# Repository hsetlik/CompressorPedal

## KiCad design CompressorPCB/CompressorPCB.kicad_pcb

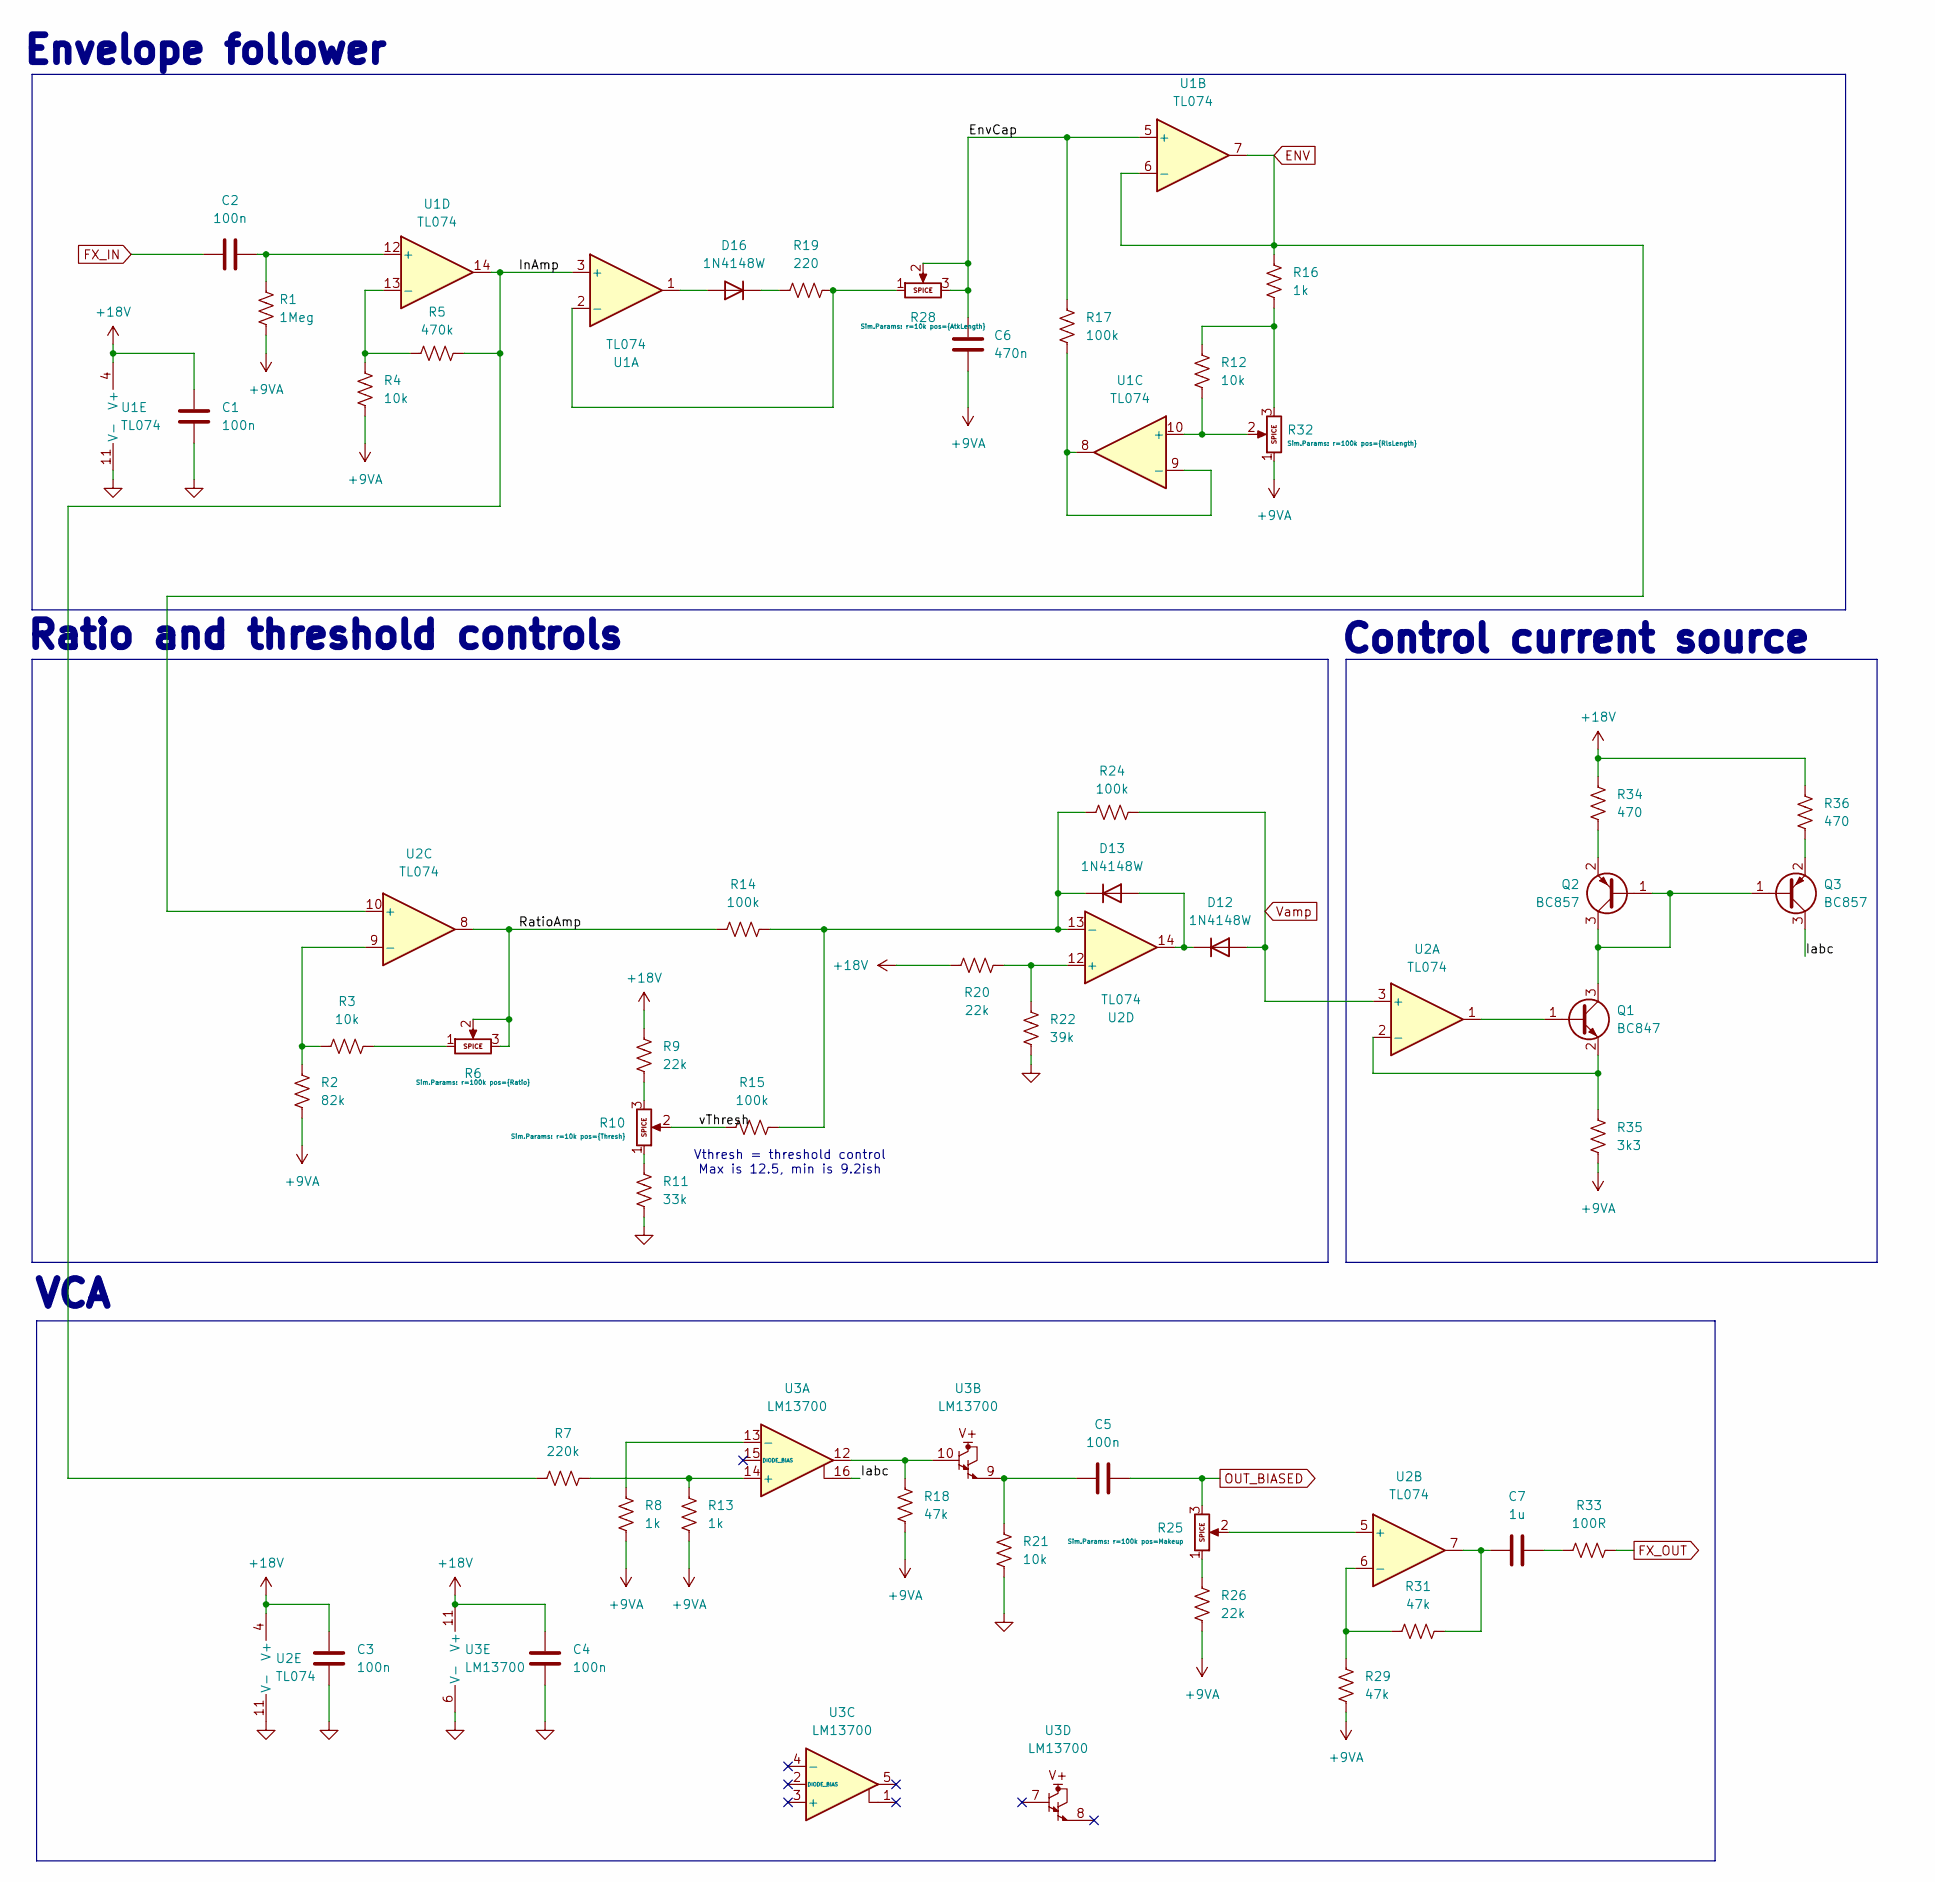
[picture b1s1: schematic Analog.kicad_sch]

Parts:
C1, C2, C3, C4, C5: 100n; C_0805_2012Metric
C6: 470n; C_0805_2012Metric
C7: 1u; C_0805_2012Metric
D12, D13, D16: 1N4148W; D_SOD-123
Q1: BC847; SOT-23
Q2, Q3: BC857; SOT-23
R1: 1Meg; R_0805_2012Metric
R2: 82k; R_0805_2012Metric
R3, R4, R12, R21: 10k; R_0805_2012Metric
R5: 470k; R_0805_2012Metric
R6, R10, R25, R28, R32: Potentiometer; Potentiometer_Alpha_RV16AF_42_Single_Long
R7: 220k; R_0805_2012Metric
R8, R13, R16: 1k; R_0805_2012Metric
R9, R20, R26: 22k; R_0805_2012Metric
R11: 33k; R_0805_2012Metric
R14, R15, R17, R24: 100k; R_0805_2012Metric
R18, R29, R31: 47k; R_0805_2012Metric
R19: 220; R_0805_2012Metric
R22: 39k; R_0805_2012Metric
R33: 100R; R_0805_2012Metric
R34, R36: 470; R_0805_2012Metric
R35: 3k3; R_0805_2012Metric
U1, U2: TL074; SOIC-14_3.9x8.7mm_P1.27mm
U3: LM13700; SOIC-16_3.9x9.9mm_P1.27mm

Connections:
+9VA: C6.2, R1.2, R2.2, R4.2, R8.2, R13.2, R18.2, R26.2, R29.1, R32.1, R35.1; also elsewhere on the board
+18V: C1.2, C3.2, C4.2, R9.1, R20.1, R34.2, R36.2, U1.4 (V+), U2.4 (V+), U3.11 (V+); also elsewhere on the board
/Analog/EnvCap: C6.1, R17.1, R28.2, R28.3, U1.5 (+)
/Analog/Iabc: Q3.3 (C), U3.16
/Analog/InAmp: R5.2, R7.1, U1.3 (+), U1.14
/Analog/RatioAmp: R6.2, R6.3, R14.1, U2.8
/Analog/vThresh: R10.2, R15.1
ENV: R16.1, U1.6 (-), U1.7, U2.10 (+); also elsewhere on the board
FX_IN: C2.1; also elsewhere on the board
FX_OUT: R33.2; also elsewhere on the board
GND: C1.1, C3.1, C4.1, R11.2, R21.2, R22.1, U1.11 (V-), U2.11 (V-), U3.6 (V-); also elsewhere on the board
unnamed: C5.1, R21.1, U3.9
unnamed: C7.1, R31.2, U2.7
unnamed: C7.2, R33.1
unnamed: D12.1 (K), D13.2 (A), U2.14
unnamed: D13.1 (K), R14.2, R15.2, R24.1, U2.13 (-)
unnamed: D16.2 (A), U1.1
unnamed: D16.1 (K), R19.1
unnamed: Q1.1 (B), U2.1
unnamed: Q1.3 (C), Q2.1 (B), Q2.3 (C), Q3.1 (B)
unnamed: Q1.2 (E), R35.2, U2.2 (-)
unnamed: Q2.2 (E), R34.1
unnamed: Q3.2 (E), R36.1
unnamed: R3.2, R6.1
unnamed: R10.1, R11.1
unnamed: R9.2, R10.3
unnamed: R12.1, R16.2, R32.3
unnamed: R18.1, U3.10, U3.12
unnamed: R25.1, R26.1
unnamed: R19.2, R28.1, U1.2 (-)
unnamed: R12.2, R32.2, U1.10 (+)
unnamed: R17.2, U1.8, U1.9 (-)
unnamed: C2.2, R1.1, U1.12 (+)
unnamed: R4.1, R5.1, U1.13 (-)
unnamed: R25.2, U2.5 (+)
unnamed: R29.2, R31.1, U2.6 (-)
unnamed: R2.1, R3.1, U2.9 (-)
unnamed: R20.2, R22.2, U2.12 (+)
unnamed: R7.2, R13.1, U3.14 (+)
unnamed: R8.1, U3.13 (-)
OUT_BIASED: C5.2, R25.3; also elsewhere on the board
Vamp: D12.2 (A), R24.2, U2.3 (+)

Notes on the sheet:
Vthresh = threshold control Max is 12.5, min is 9.2ish
Envelope follower
VCA
Control current source
Ratio and threshold controls

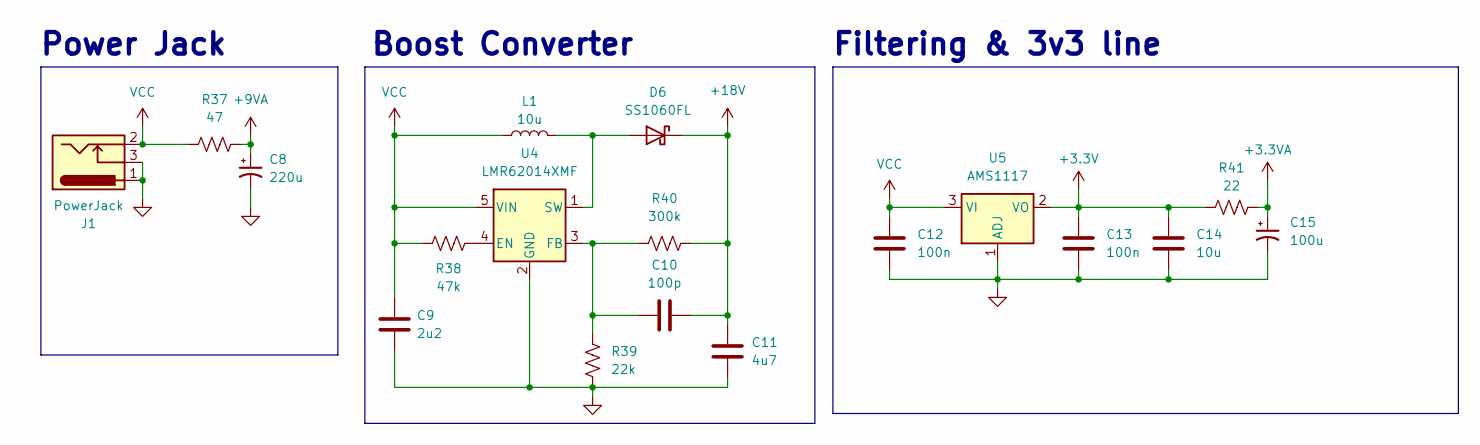
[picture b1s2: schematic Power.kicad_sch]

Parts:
C8: 220u; CP_Radial_D6.3mm_P2.50mm
C9: 2u2; C_0805_2012Metric
C10: 100p; C_0805_2012Metric
C11: 4u7; C_0805_2012Metric
C12, C13: 100n; C_0805_2012Metric; MPN KGF21BR71H104KT
C14: 10u; C_0805_2012Metric; MPN KGM21AR50J106KU
C15: 100u; CP_Radial_D6.3mm_P2.50mm
D6: SS1060FL; D_SOD-123F
J1: PowerJack; BarrelJack_Horizontal; MPN NEB 21 R-C
L1: 10u; L_SigTransformer_SLPPI04_15
R37: 47; R_0805_2012Metric
R38: 47k; R_0805_2012Metric
R39: 22k; R_0805_2012Metric
R40: 300k; R_0805_2012Metric
R41: 22; R_0805_2012Metric
U4: LMR62014XMF; SOT-23-5
U5: AMS1117; SOT-223-3_TabPin2; MPN LD1117S33CTR

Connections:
+3.3V: C13.2, C14.2, R41.2, U5.2 (VO); also elsewhere on the board
+3.3VA: C15.1, R41.1; also elsewhere on the board
+9VA: C8.1, R37.1; also elsewhere on the board
+18V: C10.2, C11.1, D6.1 (K), R40.2; also elsewhere on the board
GND: C8.2, C9.2, C11.2, C12.1, C13.1, C14.1, C15.2, J1.1, J1.3, R39.1, U4.2 (GND), U5.1 (ADJ); also elsewhere on the board
unnamed: D6.2 (A), L1.2, U4.1 (SW)
unnamed: R38.2, U4.4 (EN)
unnamed: C10.1, R39.2, R40.1, U4.3 (FB)
VCC: C9.1, C12.2, J1.2, L1.1, R37.2, R38.1, U4.5 (VIN), U5.3 (VI)

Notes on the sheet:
Filtering & 3v3 line
Boost Converter
Power Jack

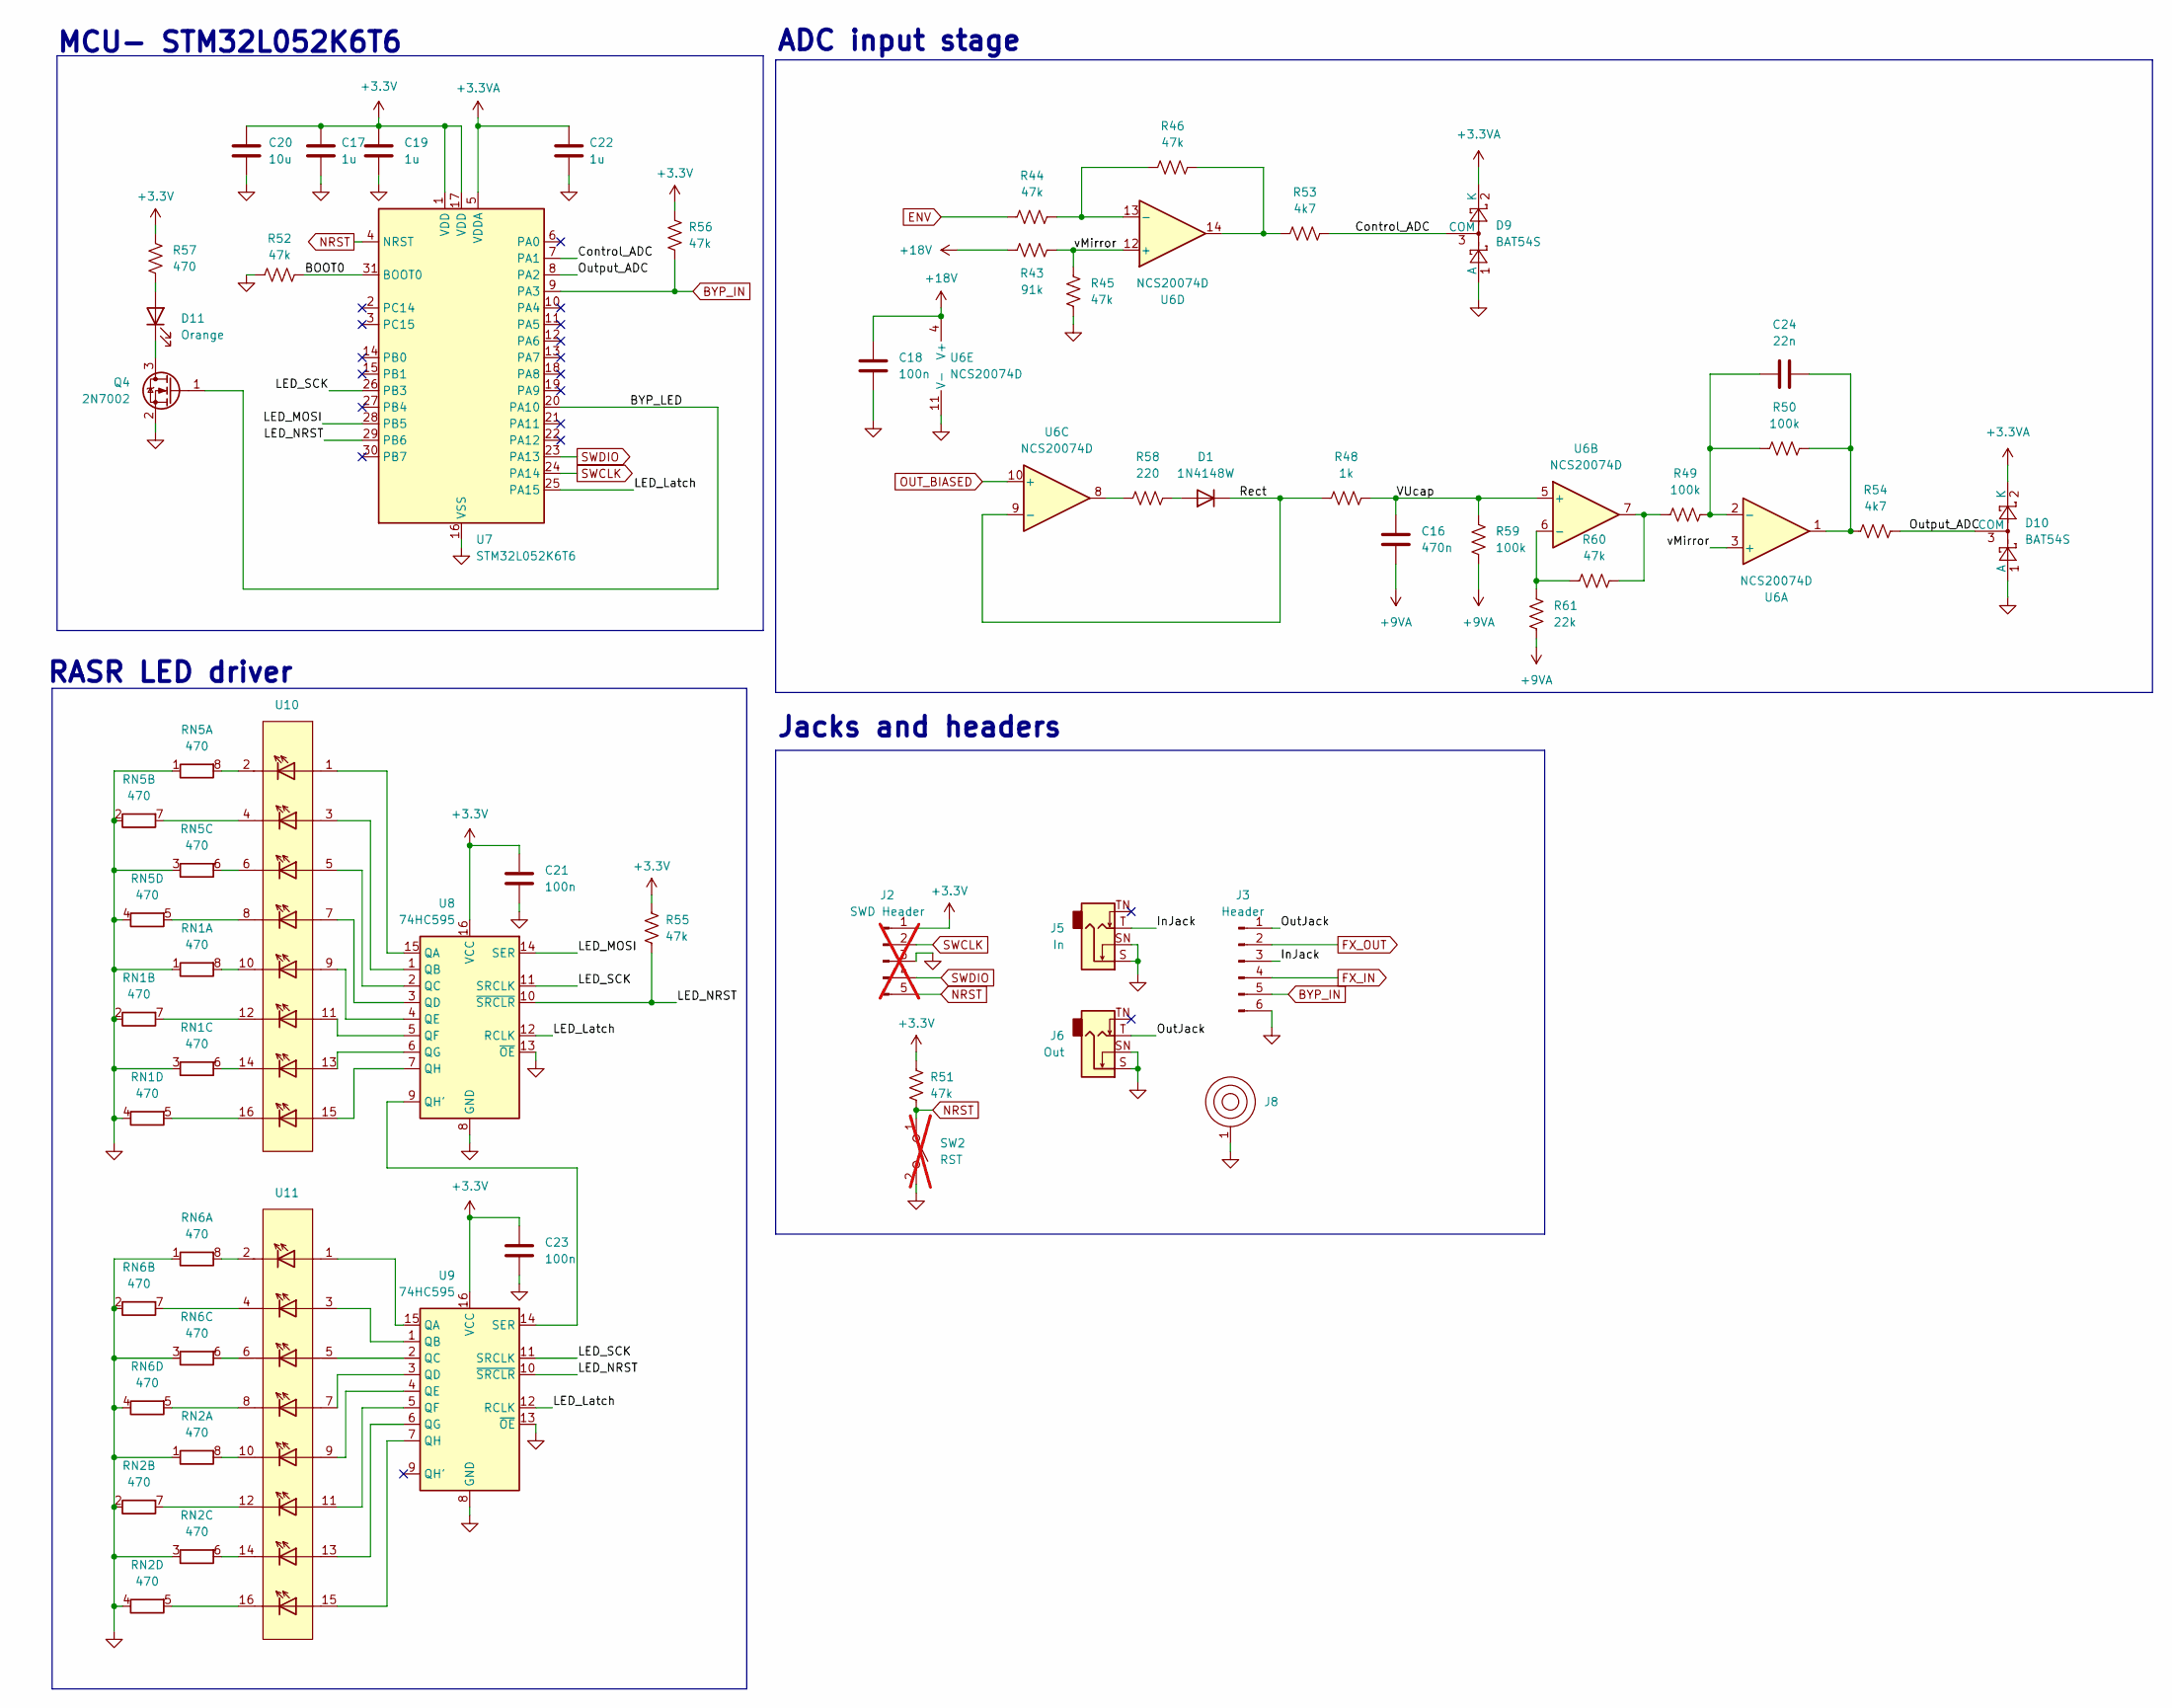
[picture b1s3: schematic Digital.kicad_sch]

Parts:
C16: 470n; C_0805_2012Metric
C17, C19, C22: 1u; C_0805_2012Metric
C18, C21, C23: 100n; C_0805_2012Metric
C20: 10u; C_0805_2012Metric
C24: 22n; C_0805_2012Metric
D1: 1N4148W; D_SOD-123
D9, D10: BAT54S; SOT-23
D11: Orange; LED_D3.0mm; MPN LTL-4291N
J2: SWD Header; PinHeader_1x05_P2.54mm_Vertical; not fitted
J3: Header; PinHeader_1x06_P2.54mm_Vertical
J5: In; Jack_6.35mm_Tayda_PJ664C_Mono_Horizontal; MPN PJ-644C MONO
J6: Out; Jack_6.35mm_Tayda_PJ664C_Mono_Horizontal; MPN PJ-644C MONO
J8: BatteryContact_Keystone_243
Q4: 2N7002; SOT-23; MPN 2N7002NXAKR
R43: 91k; R_0805_2012Metric
R44, R45, R46, R52, R60: 47k; R_0805_2012Metric
R48: 1k; R_0805_2012Metric
R49, R50, R59: 100k; R_0805_2012Metric
R51, R55, R56: 47k; R_0805_2012Metric; MPN RK73B2ATTE473J
R53, R54: 4k7; R_0805_2012Metric
R57: 470; R_0805_2012Metric; MPN RC0805JR-10470RL
R58: 220; R_0805_2012Metric
R61: 22k; R_0805_2012Metric
RN1, RN2, RN5, RN6: 470; R_Cat16-4
SW2: RST; SW_SPST_B3U-1000P; not fitted
U6: NCS20074D; SOIC-14_3.9x8.7mm_P1.27mm
U7: STM32L052K6T6; LQFP-32_7x7mm_P0.8mm
U8, U9: 74HC595; SOIC-16_3.9x9.9mm_P1.27mm
U10, U11: LED_OctoLED_0805

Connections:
+3.3V: C17.1, C19.1, C20.1, C21.1, C23.1, J2.1, R51.1, R55.1, R56.1, R57.1, U7.1 (VDD), U7.17 (VDD), U8.16 (VCC), U9.16 (VCC); also elsewhere on the board
+3.3VA: C22.1, D9.2 (K), D10.2 (K), U7.5 (VDDA); also elsewhere on the board
+9VA: C16.2, R59.1, R61.2; also elsewhere on the board
+18V: C18.1, R43.1, U6.4 (V+); also elsewhere on the board
/Digital/BOOT0: R52.2, U7.31 (BOOT0)
/Digital/BYP_LED: Q4.1 (G), U7.20 (PA10)
/Digital/Control_ADC: D9.3 (COM), R53.2, U7.7 (PA1)
/Digital/InJack: J3.3, J5.T
/Digital/LED_Latch: U7.25 (PA15), U8.12 (RCLK), U9.12 (RCLK)
/Digital/LED_MOSI: U7.28 (PB5), U8.14 (SER)
/Digital/LED_NRST: R55.2, U7.29 (PB6), U8.10 (~SRCLR), U9.10 (~SRCLR)
/Digital/LED_SCK: U7.26 (PB3), U8.11 (SRCLK), U9.11 (SRCLK)
/Digital/OutJack: J3.1, J6.T
/Digital/Output_ADC: D10.3 (COM), R54.2, U7.8 (PA2)
/Digital/Rect: D1.1 (K), R48.1, U6.9 (-)
/Digital/VUcap: C16.1, R48.2, R59.2, U6.5 (+)
/Digital/vMirror: R43.2, R45.2, U6.3 (+), U6.12 (+)
BYP_IN: J3.5, R56.2, U7.9 (PA3)
ENV: R44.1; also elsewhere on the board
FX_IN: J3.4; also elsewhere on the board
FX_OUT: J3.2; also elsewhere on the board
GND: C17.2, C18.2, C19.2, C20.2, C21.2, C22.2, C23.2, D9.1 (A), D10.1 (A), J2.3, J3.6, J5.S, J5.SN, J6.S, J6.SN, J8.1, Q4.2 (S), R45.1, R52.1, RN1.1 (R1.1), RN1.2 (R2.1), RN1.3 (R3.1), RN1.4 (R4.1), RN2.1 (R1.1), RN2.2 (R2.1), RN2.3 (R3.1), RN2.4 (R4.1), RN5.1 (R1.1), RN5.2 (R2.1), RN5.3 (R3.1), RN5.4 (R4.1), RN6.1 (R1.1), RN6.2 (R2.1), RN6.3 (R3.1), RN6.4 (R4.1), SW2.2 (B), U6.11 (V-), U7.16 (VSS), U7.32 (VSS), U8.8 (GND), U8.13 (~OE), U9.8 (GND), U9.13 (~OE); also elsewhere on the board
NRST: J2.5, R51.2, SW2.1 (A), U7.4 (NRST)
unnamed: C24.2, R50.2, R54.1, U6.1
unnamed: D1.2 (A), R58.2
unnamed: D11.2 (A), R57.2
unnamed: D11.1 (K), Q4.3 (D)
unnamed: R46.2, R53.1, U6.14
unnamed: R49.1, R60.1, U6.7
unnamed: R58.1, U6.8
unnamed: RN1.8 (R1.2), U10.10 (2)
unnamed: RN1.7 (R2.2), U10.12 (2)
unnamed: RN1.6 (R3.2), U10.14 (2)
unnamed: RN1.5 (R4.2), U10.16 (2)
unnamed: RN2.8 (R1.2), U11.10 (2)
unnamed: RN2.7 (R2.2), U11.12 (2)
unnamed: RN2.6 (R3.2), U11.14 (2)
unnamed: RN2.5 (R4.2), U11.16 (2)
unnamed: RN5.8 (R1.2), U10.2
unnamed: RN5.7 (R2.2), U10.4 (2)
unnamed: RN5.6 (R3.2), U10.6 (2)
unnamed: RN5.5 (R4.2), U10.8 (2)
unnamed: RN6.8 (R1.2), U11.2
unnamed: RN6.7 (R2.2), U11.4 (2)
unnamed: RN6.6 (R3.2), U11.6 (2)
unnamed: RN6.5 (R4.2), U11.8 (2)
unnamed: C24.1, R49.2, R50.1, U6.2 (-)
unnamed: R60.2, R61.1, U6.6 (-)
unnamed: R44.2, R46.1, U6.13 (-)
unnamed: U8.15 (QA), U10.1
unnamed: U8.1 (QB), U10.3 (1)
unnamed: U8.2 (QC), U10.5 (1)
unnamed: U8.3 (QD), U10.7 (1)
unnamed: U8.4 (QE), U10.9 (1)
unnamed: U8.5 (QF), U10.11 (1)
unnamed: U8.6 (QG), U10.13 (1)
unnamed: U8.9 (QH'), U9.14 (SER)
unnamed: U8.7 (QH), U10.15 (1)
unnamed: U9.15 (QA), U11.1
unnamed: U9.1 (QB), U11.3 (1)
unnamed: U9.2 (QC), U11.5 (1)
unnamed: U9.3 (QD), U11.7 (1)
unnamed: U9.4 (QE), U11.9 (1)
unnamed: U9.5 (QF), U11.11 (1)
unnamed: U9.6 (QG), U11.13 (1)
unnamed: U9.7 (QH), U11.15 (1)
OUT_BIASED: U6.10 (+); also elsewhere on the board
SWCLK: J2.2, U7.24 (PA14)
SWDIO: J2.4, U7.23 (PA13)

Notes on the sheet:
ADC input stage
Jacks and headers
MCU- STM32L052K6T6
RASR LED driver

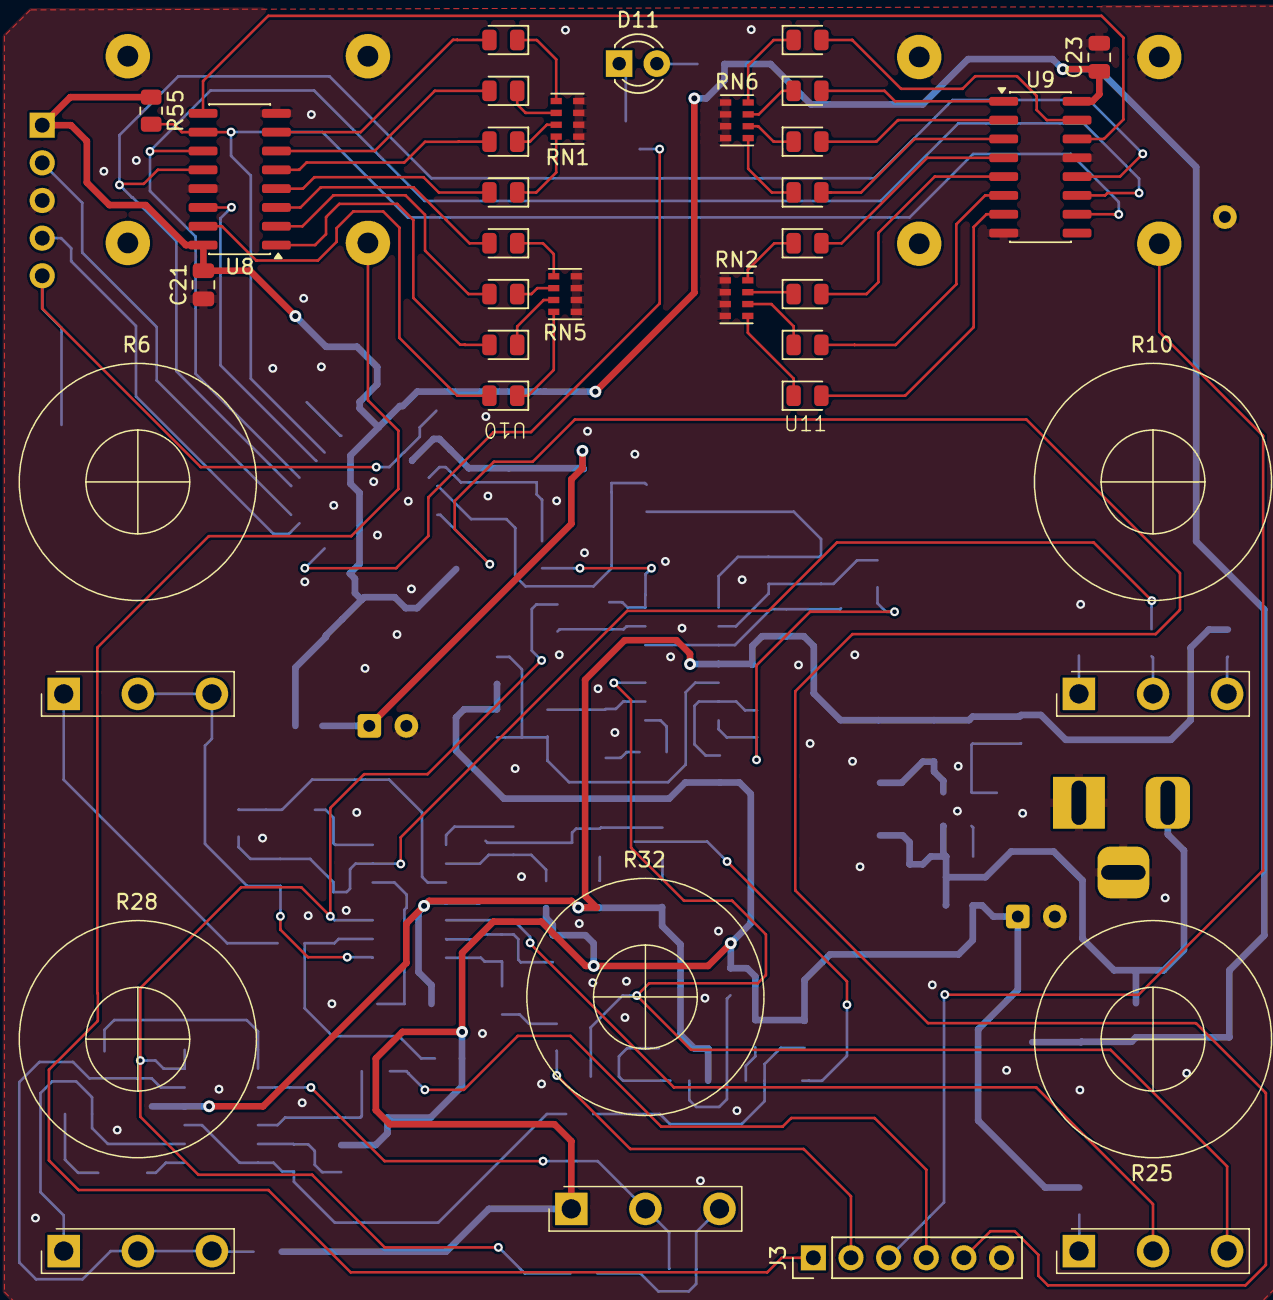
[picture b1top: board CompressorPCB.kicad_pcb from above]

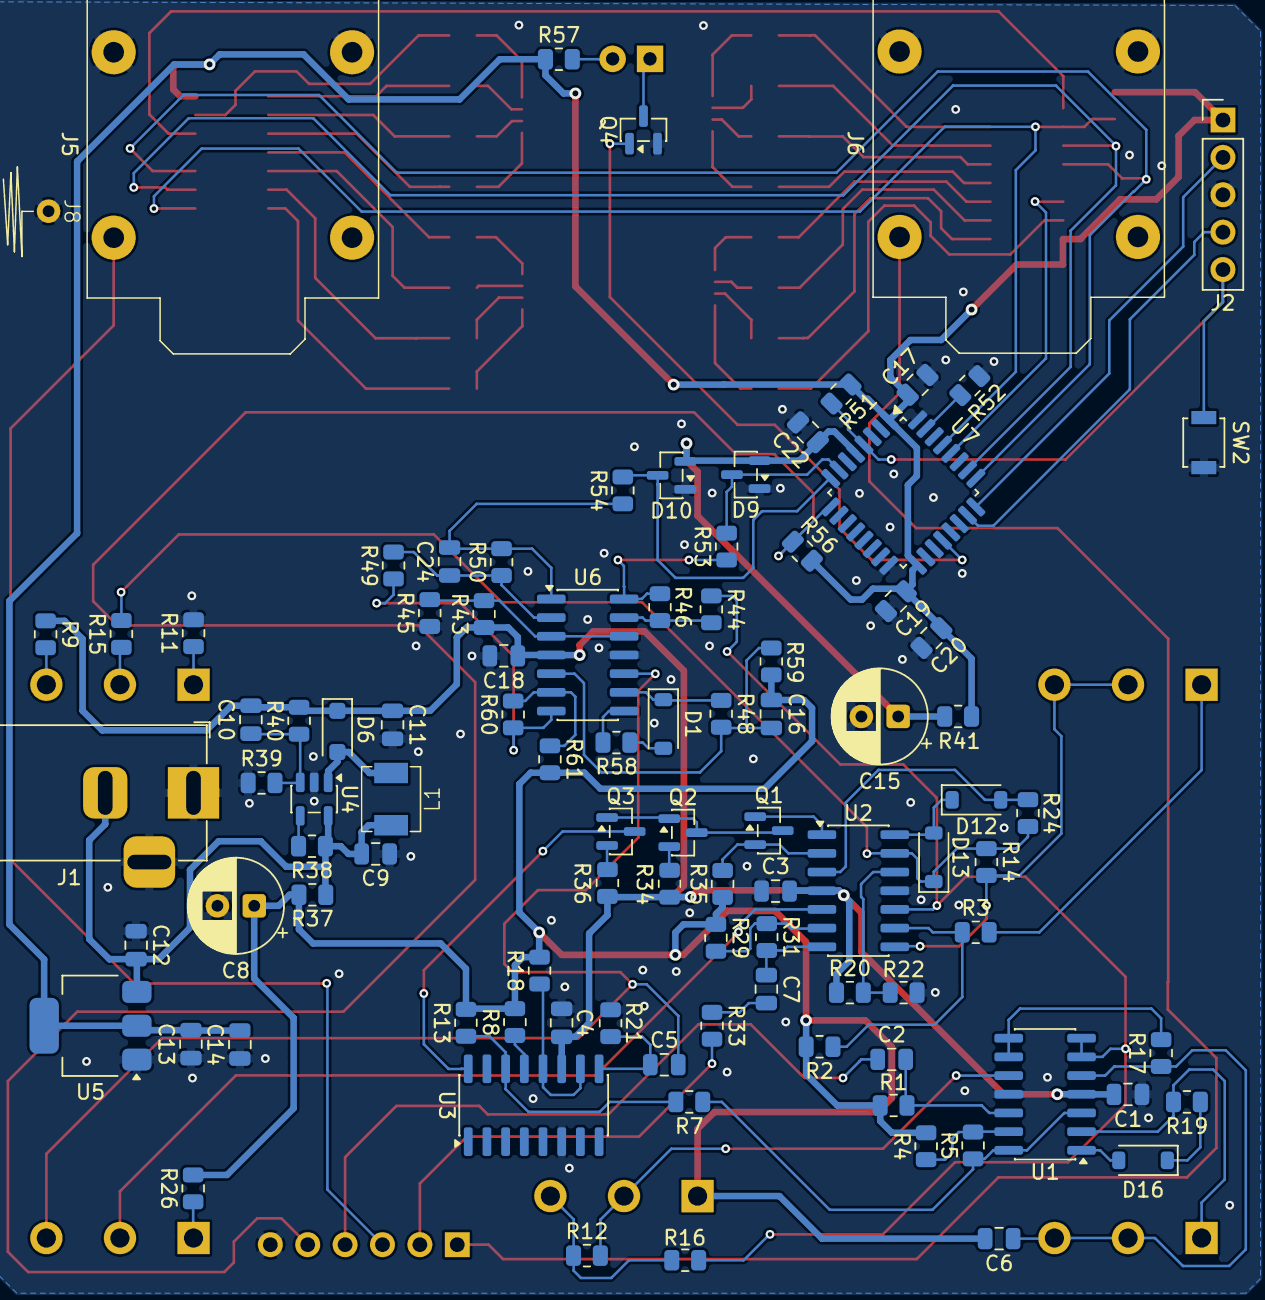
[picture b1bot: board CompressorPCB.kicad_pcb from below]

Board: 4 copper layers, 115 parts (97 on the bottom side), 108 nets.

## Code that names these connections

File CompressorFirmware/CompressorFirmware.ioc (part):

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Mcu.Name=STM32L052K(6-8)Tx
Mcu.Package=LQFP32
Mcu.UserName=STM32L052K6Tx
PA1.GPIOParameters=GPIO_Label
PA1.GPIO_Label=CONTROL_ADC
PA1.Mode=IN1
PA1.Signal=ADC_IN1
PA10.GPIOParameters=GPIO_PuPd,GPIO_Label
PA10.GPIO_Label=BYP_LED
PA10.GPIO_PuPd=GPIO_PULLDOWN
PA10.Signal=GPIO_Output
PA13.Mode=Serial_Wire
PA13.Signal=SYS_SWDIO
PA14.Mode=Serial_Wire
PA14.Signal=SYS_SWCLK
PA15.GPIOParameters=GPIO_Label
PA15.GPIO_Label=LED_LATCH
PA15.Mode=NSS_Signal_Hard_Output
PA15.Signal=SPI1_NSS
PA2.GPIOParameters=GPIO_Label
PA2.GPIO_Label=OUTPUT_ADC
PA2.Mode=IN2
PA2.Signal=ADC_IN2
PA3.GPIOParameters=GPIO_Label
PA3.GPIO_Label=BYP_IN
PA3.Signal=GPIO_Input
PB3.GPIOParameters=GPIO_Label
PB3.GPIO_Label=LED_SCK
PB3.Mode=TX_Only_Simplex_Unidirect_Master
PB3.Signal=SPI1_SCK
PB5.GPIOParameters=GPIO_Label
PB5.GPIO_Label=LED_MOSI
PB5.Mode=TX_Only_Simplex_Unidirect_Master
PB5.Signal=SPI1_MOSI
PB6.GPIOParameters=GPIO_Label
PB6.GPIO_Label=LED_NRST
PB6.Signal=GPIO_Output
RCC.SYSCLKFreq_VALUE=24000000
RCC.SYSCLKSource=RCC_SYSCLKSOURCE_PLLCLK
board=custom
